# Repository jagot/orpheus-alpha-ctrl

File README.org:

#+TITLE: Ορφέας Άλφα controller
#+AUTHOR: Stefanos Carlström
#+EMAIL: stefanos.carlstrom@gmail.com

Small breakout board for a NodeMCU microcontroller to be used in
conjunction with a [[http://github.com/jagot/orpheus-alpha][Ορφέας Άλφα]] preamplifier. The board provides
connectability to a rotary encoder and an optional Neopixel ring (for
e.g. volume level display). Since the NodeMCU provides WiFi connection
as well, the board can (if desired) be used without a rotary encoder.

[[orpheus-alpha-ctrl.pdf][Schematic]]

[[orpheus-alpha-ctrl.png]]

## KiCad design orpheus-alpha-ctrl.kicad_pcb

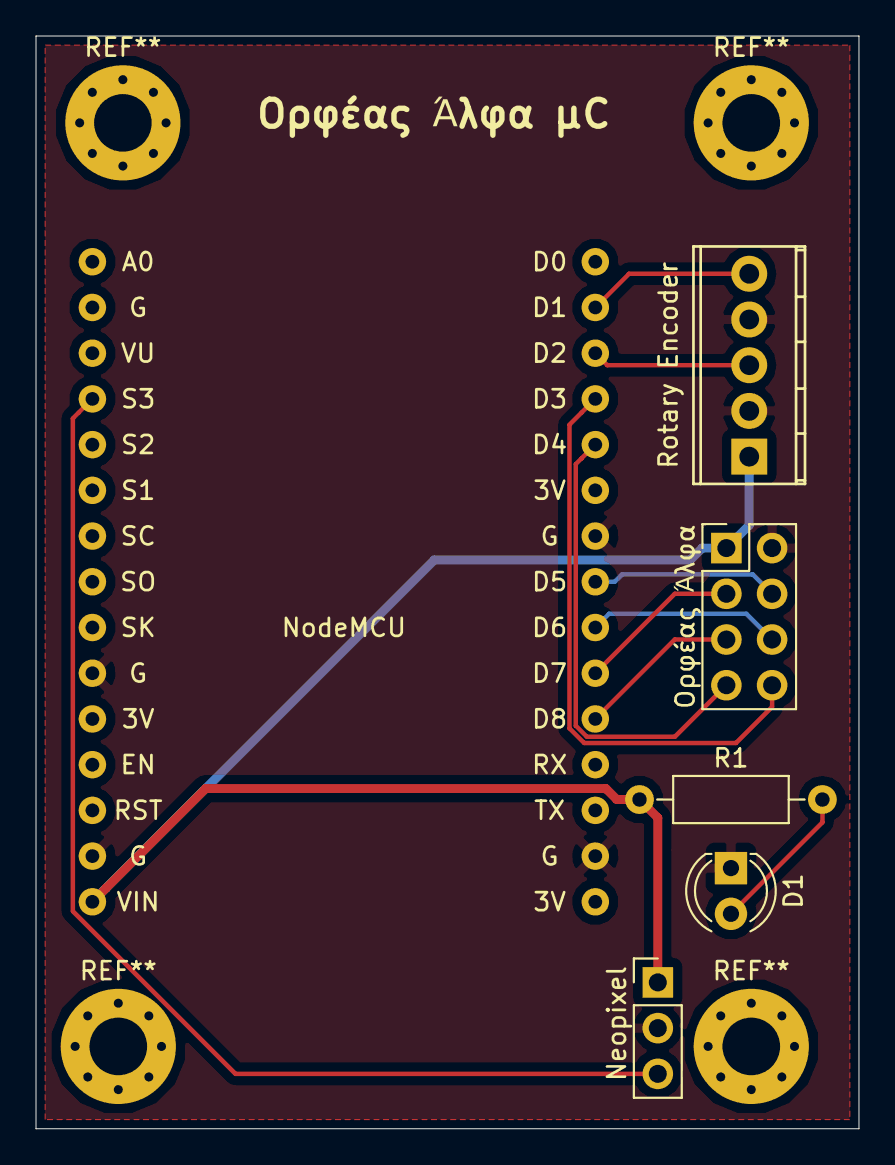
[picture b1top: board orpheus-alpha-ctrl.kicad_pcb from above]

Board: 2 copper layers, 45.7 x 60.7 mm, 6 parts (0 on the bottom side), 12 nets.

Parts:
D1: LED; LED_D4.0mm
Neopixel: CONN_01X03_MALE; Pin_Header_Straight_1x03_Pitch2.54mm
NodeMCU: NodeMCU1.0(ESP-12E); NodeMCU1.0(12-E)
R1: R; R_Axial_DIN0207_L6.3mm_D2.5mm_P10.16mm_Horizontal
Rotary Encoder: Screw_Terminal_1x05; TerminalBlock_Pheonix_MPT-2.54mm_5pol
Ορφέας Άλφα: CONN_02X04; Pin_Header_Straight_2x04_Pitch2.54mm

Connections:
CLK: NodeMCU.23, Ορφέας Άλφα.4
CS: NodeMCU.20, Ορφέας Άλφα.5
GNDD: D1.1, Neopixel.2, NodeMCU.10, NodeMCU.14, NodeMCU.17, NodeMCU.24, Rotary Encoder.2, Rotary Encoder.4, Ορφέας Άλφα.2
Mute: NodeMCU.27, Ορφέας Άλφα.8
NEO: Neopixel.3, NodeMCU.4
unnamed: D1.2, R1.2
ROT1: NodeMCU.28, Rotary Encoder.3
ROT2: NodeMCU.29, Rotary Encoder.5
SDI: NodeMCU.21, Ορφέας Άλφα.3
SDO: NodeMCU.22, Ορφέας Άλφα.6
VD: Neopixel.1, NodeMCU.15, R1.1, Rotary Encoder.1, Ορφέας Άλφα.1
Zcen: NodeMCU.26, Ορφέας Άλφα.7

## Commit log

2020-08-08 Added sample source code
